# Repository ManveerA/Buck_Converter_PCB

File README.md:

Repository for Buck Converter PCB design project for ELEC-4450 Power Electronics.

See ELEC-4500 - Project Report.pdf for pictures of the board and see ELEC-4500 - Preliminary Design.pdf for the simulations and initial design.

Author: Manveer Aujla

Contact: aujla21@uwindsor.ca (school) | manveeraujla0226@gmail.com (personal) 

Last updated: 2025-04-23

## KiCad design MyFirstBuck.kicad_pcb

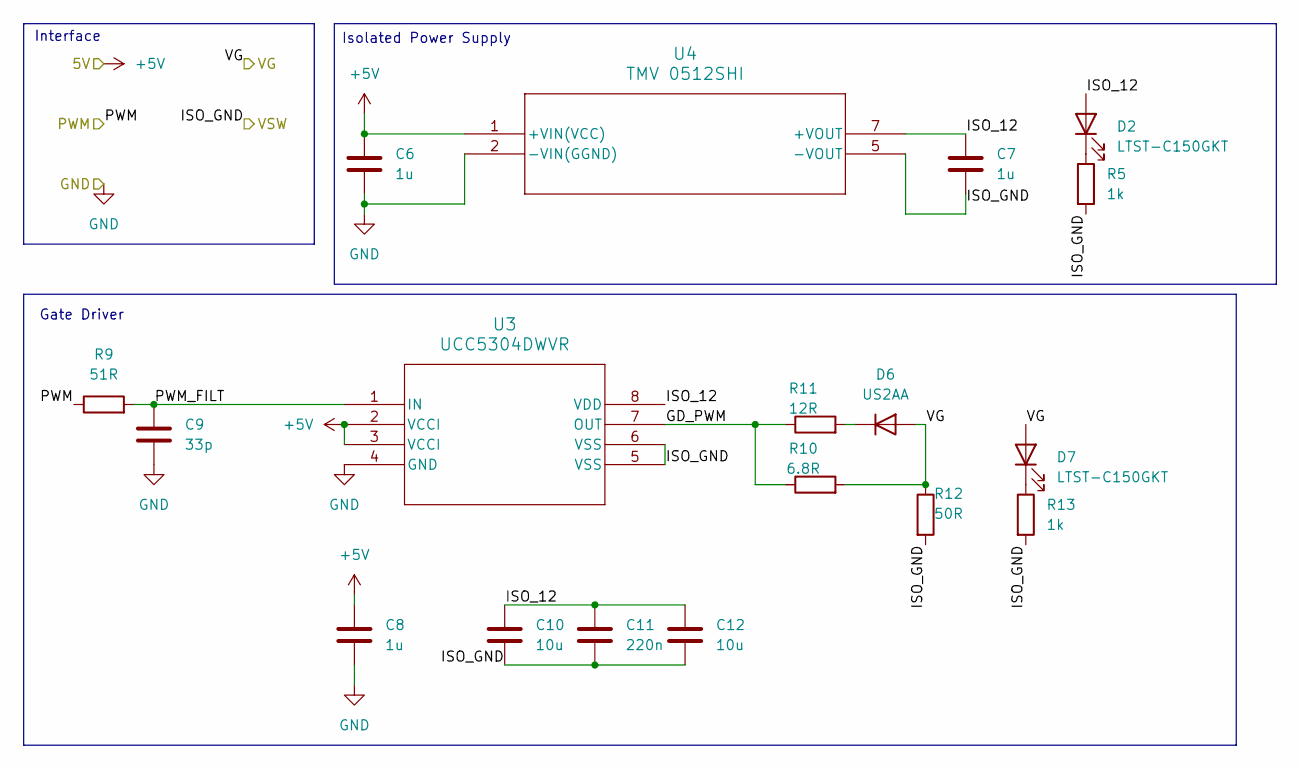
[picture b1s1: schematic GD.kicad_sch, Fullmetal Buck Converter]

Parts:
C6, C7, C8: 1u; C_0805_2012Metric_Pad1.18x1.45mm_HandSolder; Part Number TMCP1D105MTRF
C9: 33p; C_0805_2012Metric_Pad1.18x1.45mm_HandSolder; Part Number C0805C330K5GACTU
C10: 10u; C_0805_2012Metric_Pad1.18x1.45mm_HandSolder; Part Number F951C106MPAAQ2
C11: 220n; C_0805_2012Metric_Pad1.18x1.45mm_HandSolder; Part Number C0805C224K5RACTU
C12: 10u; C_0805_2012Metric_Pad1.18x1.45mm_HandSolder; Part Number GRM21BR61E106KA73L
D2, D7: LTST-C150GKT; LED_1206_3216Metric_Pad1.42x1.75mm_HandSolder; Part Number LTST-C150GKT
D6: US2AA; D_SMA_Handsoldering; Part Number US2AA
R5, R13: 1k; R_0805_2012Metric_Pad1.20x1.40mm_HandSolder; Part Number RMCF0805FT1K00
R9: 51R; R_0805_2012Metric_Pad1.20x1.40mm_HandSolder; Part Number RC0805FR-0751RL
R10: 6.8R; R_0805_2012Metric_Pad1.20x1.40mm_HandSolder; Part Number RCS08056R80FKEA
R11: 12R; R_0805_2012Metric_Pad1.20x1.40mm_HandSolder; Part Number ERJ-P06J120V
R12: 50R; R_1206_3216Metric_Pad1.30x1.75mm_HandSolder; Part Number RCP1206W50R0GEB
U3: UCC5304DWVR; SOIC8_DWV_TEX; Part Number UCC5304DWVR
U4: TMV 0512SHI; TMV-HI_SINGLE_TRP; Part Number TMV 0512SHI

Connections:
+5V: C6.1, C8.1, U3.2 (VCCI), U3.3 (VCCI), U4.1 (+VIN(VCC)); also elsewhere on the board
/GD/GD_PWM: R10.1, R11.1, U3.7 (OUT)
/GD/ISO_12: C7.1, C10.1, C11.1, C12.1, D2.2 (A), U3.8 (VDD), U4.7 (+VOUT)
/GD/PWM_FILT: C9.1, R9.2, U3.1 (IN)
/PWM: R9.1; also elsewhere on the board
/VG: D6.2 (A), D7.2 (A), R10.2, R12.1; also elsewhere on the board
/VSW: C7.2, C10.2, C11.2, C12.2, R5.2, R12.2, R13.2, U3.5 (VSS), U3.6 (VSS), U4.5 (-VOUT); also elsewhere on the board
GND: C6.2, C8.2, C9.2, U3.4 (GND), U4.2 (-VIN(GGND)); also elsewhere on the board
unnamed: D2.1 (K), R5.1
unnamed: D6.1 (K), R11.2
unnamed: D7.1 (K), R13.1

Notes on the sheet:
Interface
Isolated Power Supply
Gate Driver

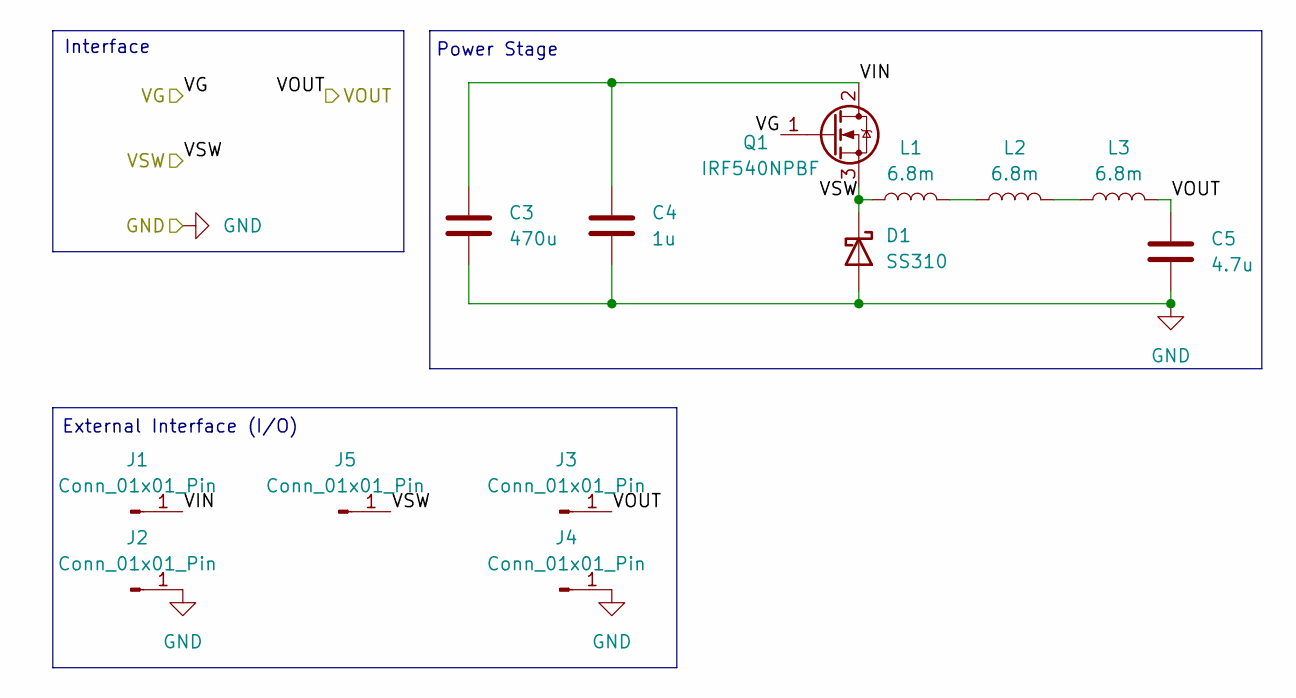
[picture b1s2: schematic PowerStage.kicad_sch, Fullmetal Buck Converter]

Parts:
C3: 470u; CP_Radial_D18.0mm_P7.50mm; Part Number 100ZLH470MEFC16X31.5
C4: 1u; C_0805_2012Metric_Pad1.18x1.45mm_HandSolder; Part Number GRM21BC72A105KE01L
C5: 4.7u; C_1206_3216Metric_Pad1.33x1.80mm_HandSolder; Part Number GRM31CC72A475KE11L
D1: SS310; D_SMA_Handsoldering; Part Number SS310
J1, J2, J3, J4, J5: Conn_01x01_Pin; Banana_Jack_1Pin; Part Number BU-P72930-2
L1, L2, L3: 6.8m; L_Radial_D24.4mm_P23.10mm_Murata_1400series; Part Number 1468507C
Q1: IRF540NPBF; TO-220-3_Vertical; Part Number IRF540NPBF

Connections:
/PowerStage/VIN: C3.1, C4.1, J1.1, Q1.2 (D)
/VG: Q1.1 (G); also elsewhere on the board
/VOUT: C5.1, J3.1, L3.2; also elsewhere on the board
/VSW: D1.1 (K), J5.1, L1.1, Q1.3 (S); also elsewhere on the board
GND: C3.2, C4.2, C5.2, D1.2 (A), J2.1, J4.1; also elsewhere on the board
unnamed: L1.2, L2.1
unnamed: L2.2, L3.1

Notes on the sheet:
External Interface (I/O)
Interface
Power Stage

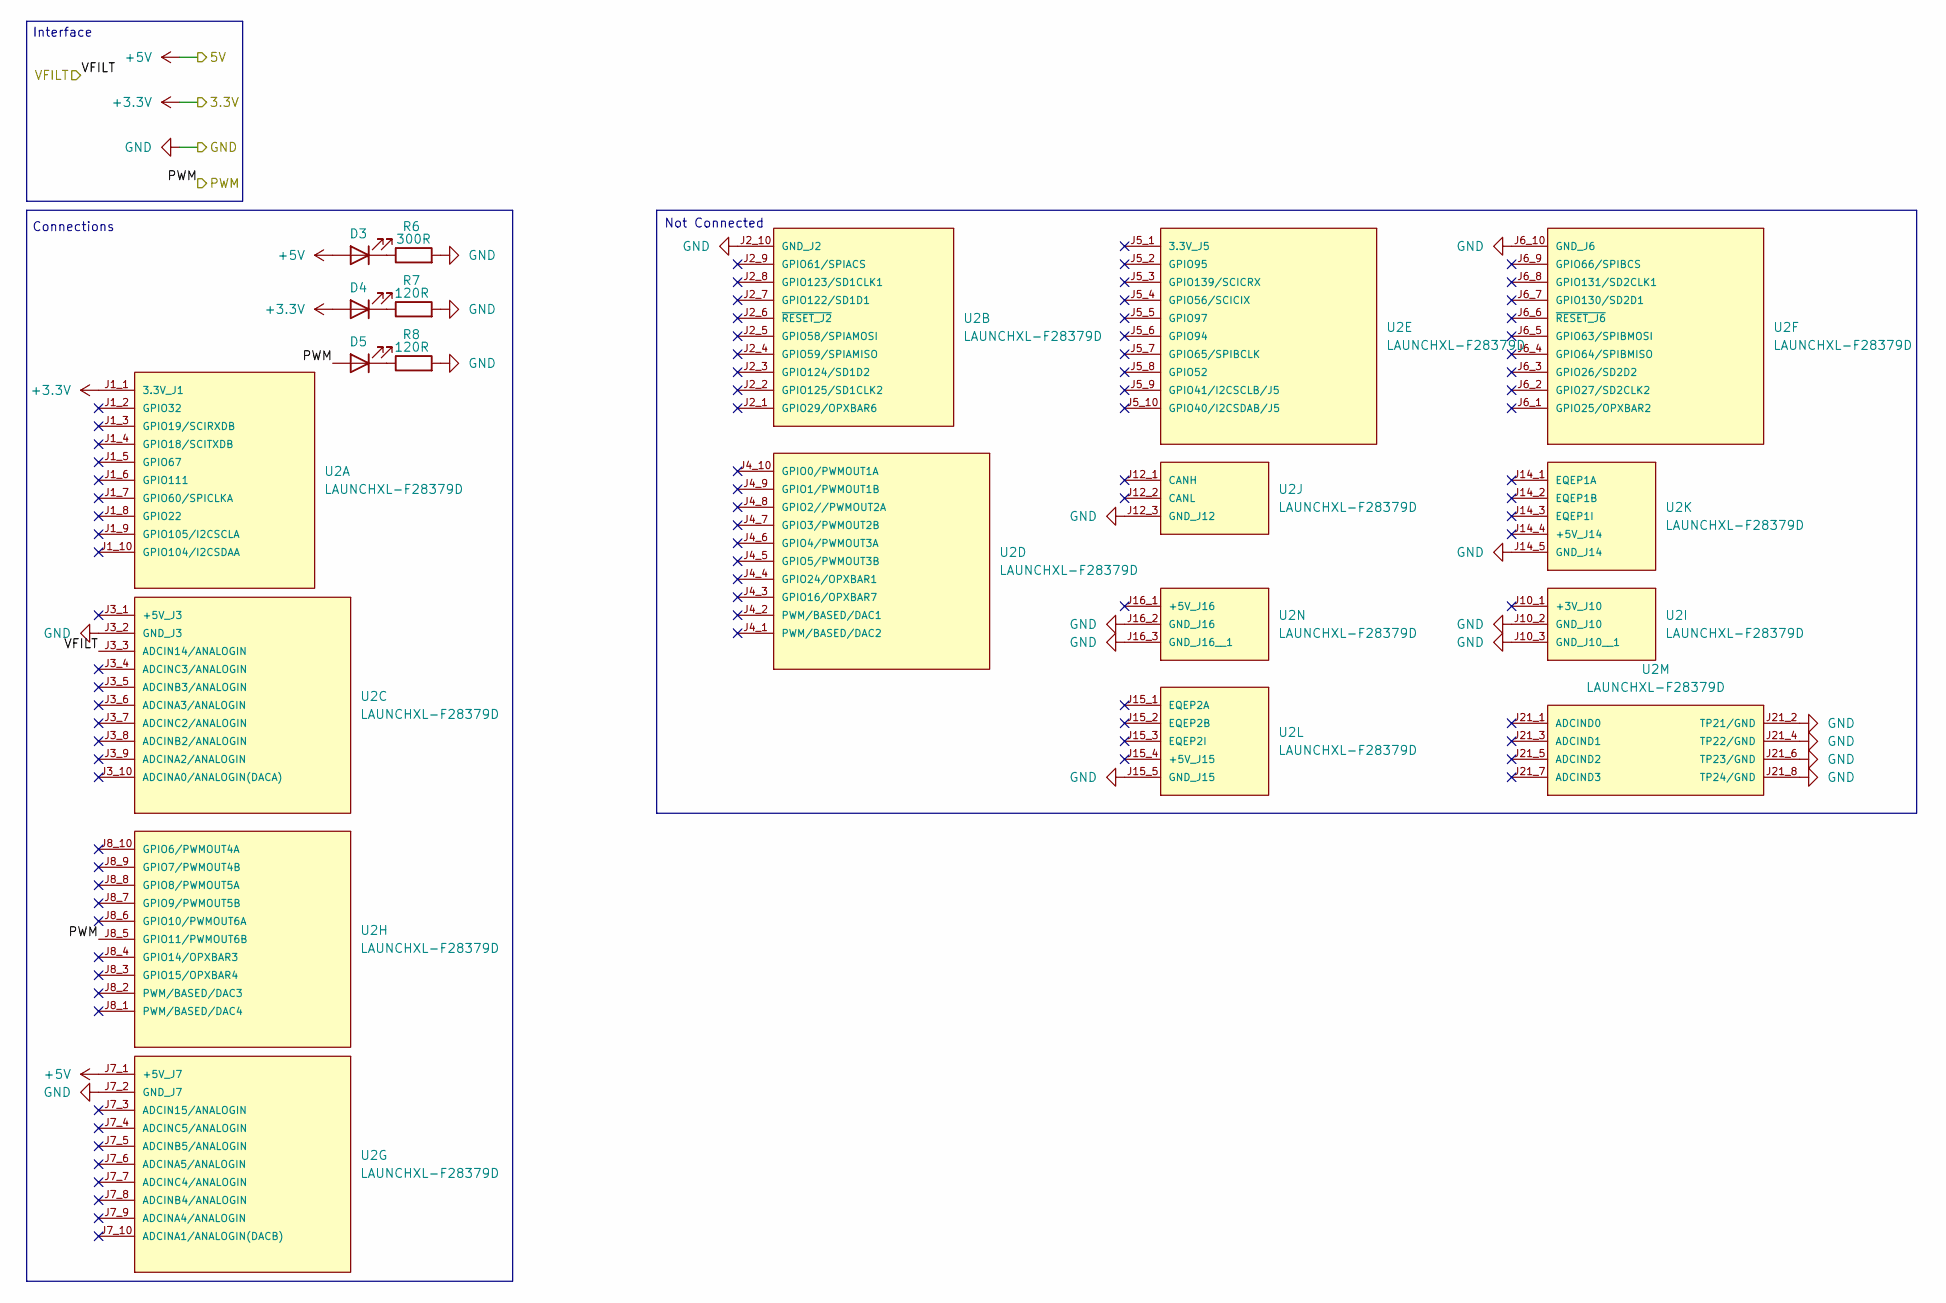
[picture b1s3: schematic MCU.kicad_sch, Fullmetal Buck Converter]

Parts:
D3, D4, D5: LTST-C150GKT; LED_1206_3216Metric_Pad1.42x1.75mm_HandSolder; Part Number LTST-C150GKT
R6: 300R; R_0805_2012Metric_Pad1.20x1.40mm_HandSolder; Part Number RMCF0805JT300R
R7, R8: 120R; R_0805_2012Metric_Pad1.20x1.40mm_HandSolder; Part Number RMCF0805FT120R
U2: LAUNCHXL-F28379D; MOD_LAUNCHXL-F28379D; PARTREV 2.0

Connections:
+3.3V: D4.2 (A), U2.J1_1 (3.3V_J1); also elsewhere on the board
+5V: D3.2 (A), U2.J7_1 (+5V_J7); also elsewhere on the board
/PWM: D5.2 (A), U2.J8_5 (GPIO11/PWMOUT6B); also elsewhere on the board
/VFILT: U2.J3_3 (ADCIN14/ANALOGIN); also elsewhere on the board
GND: R6.2, R7.2, R8.2, U2.J2_10 (GND_J2), U2.J3_2 (GND_J3), U2.J6_10 (GND_J6), U2.J7_2 (GND_J7), U2.J10_2 (GND_J10), U2.J10_3 (GND_J10__1), U2.J12_3 (GND_J12), U2.J14_5 (GND_J14), U2.J15_5 (GND_J15), U2.J16_2 (GND_J16), U2.J16_3 (GND_J16__1), U2.J21_2 (TP21/GND), U2.J21_4 (TP22/GND), U2.J21_6 (TP23/GND), U2.J21_8 (TP24/GND); also elsewhere on the board
unnamed: D3.1 (K), R6.1
unnamed: D4.1 (K), R7.1
unnamed: D5.1 (K), R8.1

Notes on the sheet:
Interface
Not Connected
Connections

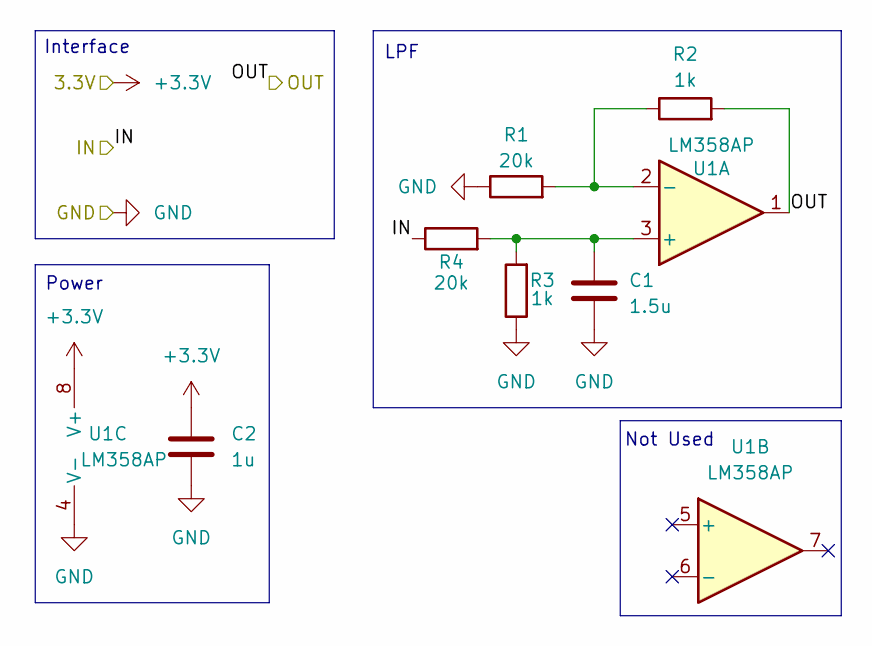
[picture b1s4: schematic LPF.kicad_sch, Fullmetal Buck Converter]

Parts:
C1: 1.5u; C_0805_2012Metric_Pad1.18x1.45mm_HandSolder; Part Number CGA4J3X7R1H155K125AB
C2: 1u; C_0805_2012Metric_Pad1.18x1.45mm_HandSolder; Part Number TMCP1D105MTRF
R1, R4: 20k; R_0805_2012Metric_Pad1.20x1.40mm_HandSolder; Part Number RC0805FR-0720KL
R2, R3: 1k; R_0805_2012Metric_Pad1.20x1.40mm_HandSolder; Part Number RMCF0805FT1K00
U1: LM358AP; DIP794W45P254L959H508Q8; Part Number LM358AP

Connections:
+3.3V: C2.1, U1.8 (V+); also elsewhere on the board
/VFILT: R2.2, U1.1; also elsewhere on the board
/VOUT: R4.1; also elsewhere on the board
GND: C1.2, C2.2, R1.1, R3.1, U1.4 (V-); also elsewhere on the board
unnamed: C1.1, R3.2, R4.2, U1.3 (+)
unnamed: R1.2, R2.1, U1.2 (-)

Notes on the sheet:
Power
Interface
Not Used
LPF

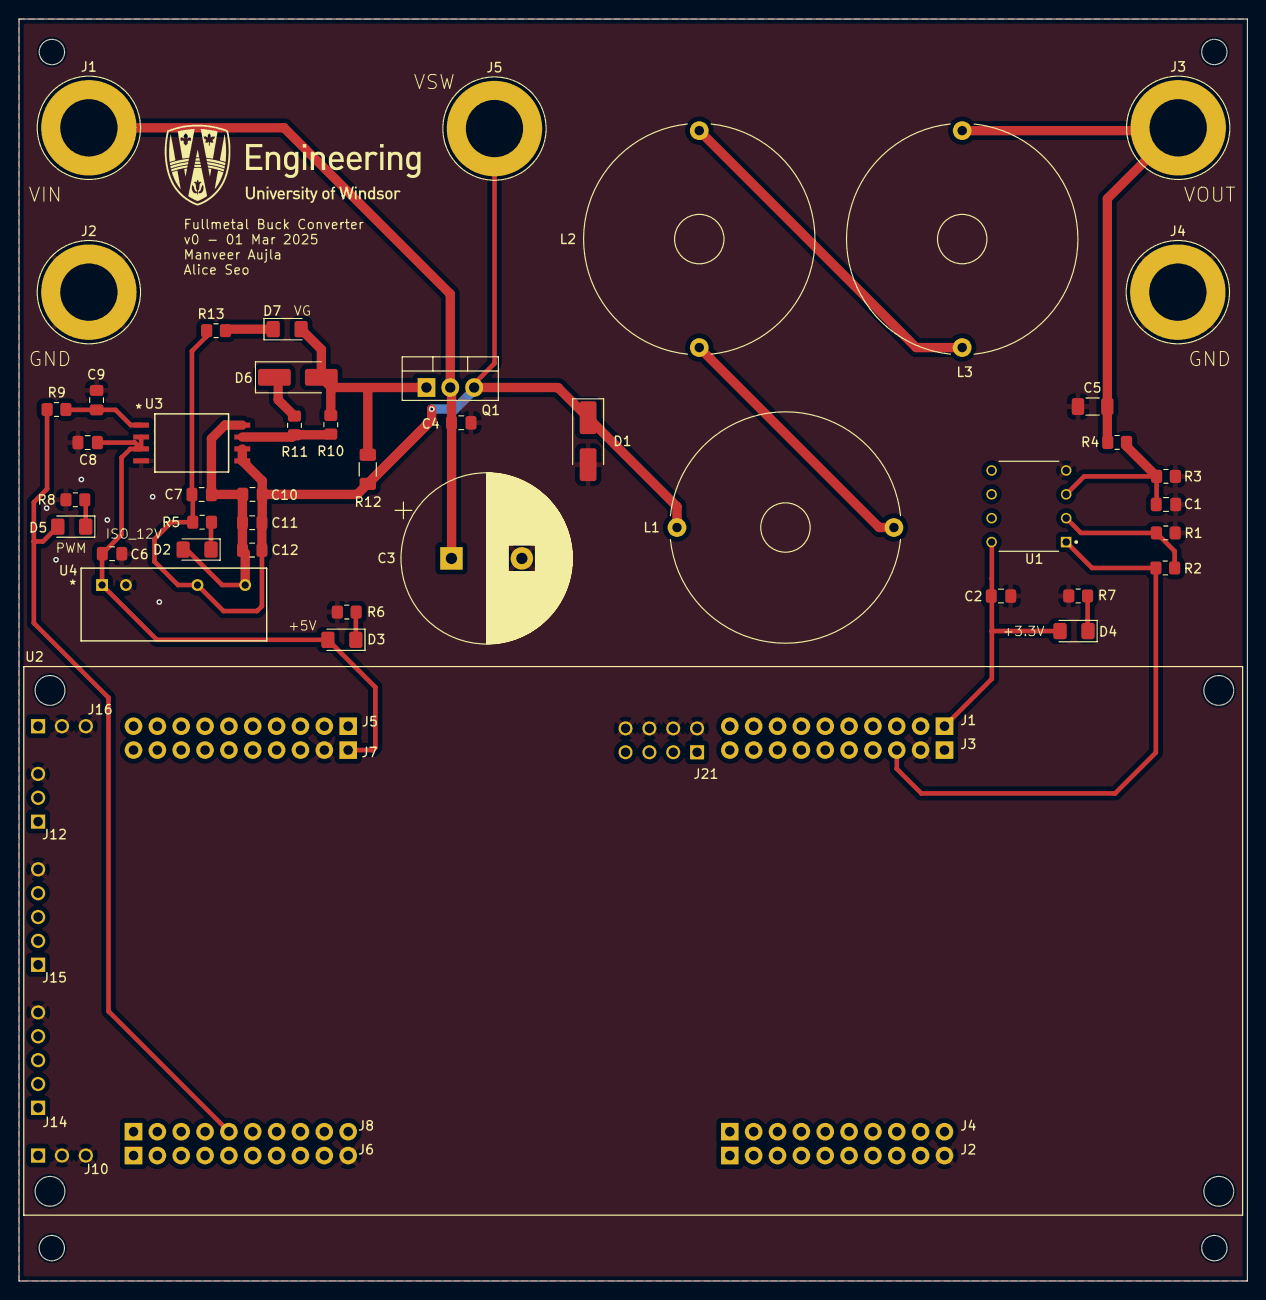
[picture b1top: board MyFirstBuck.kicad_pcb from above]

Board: 2 copper layers, 130.8 x 134.4 mm, 45 parts (0 on the bottom side), 22 nets.

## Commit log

2025-02-24 Create Test
2025-03-02 Create Digikey_Cart
